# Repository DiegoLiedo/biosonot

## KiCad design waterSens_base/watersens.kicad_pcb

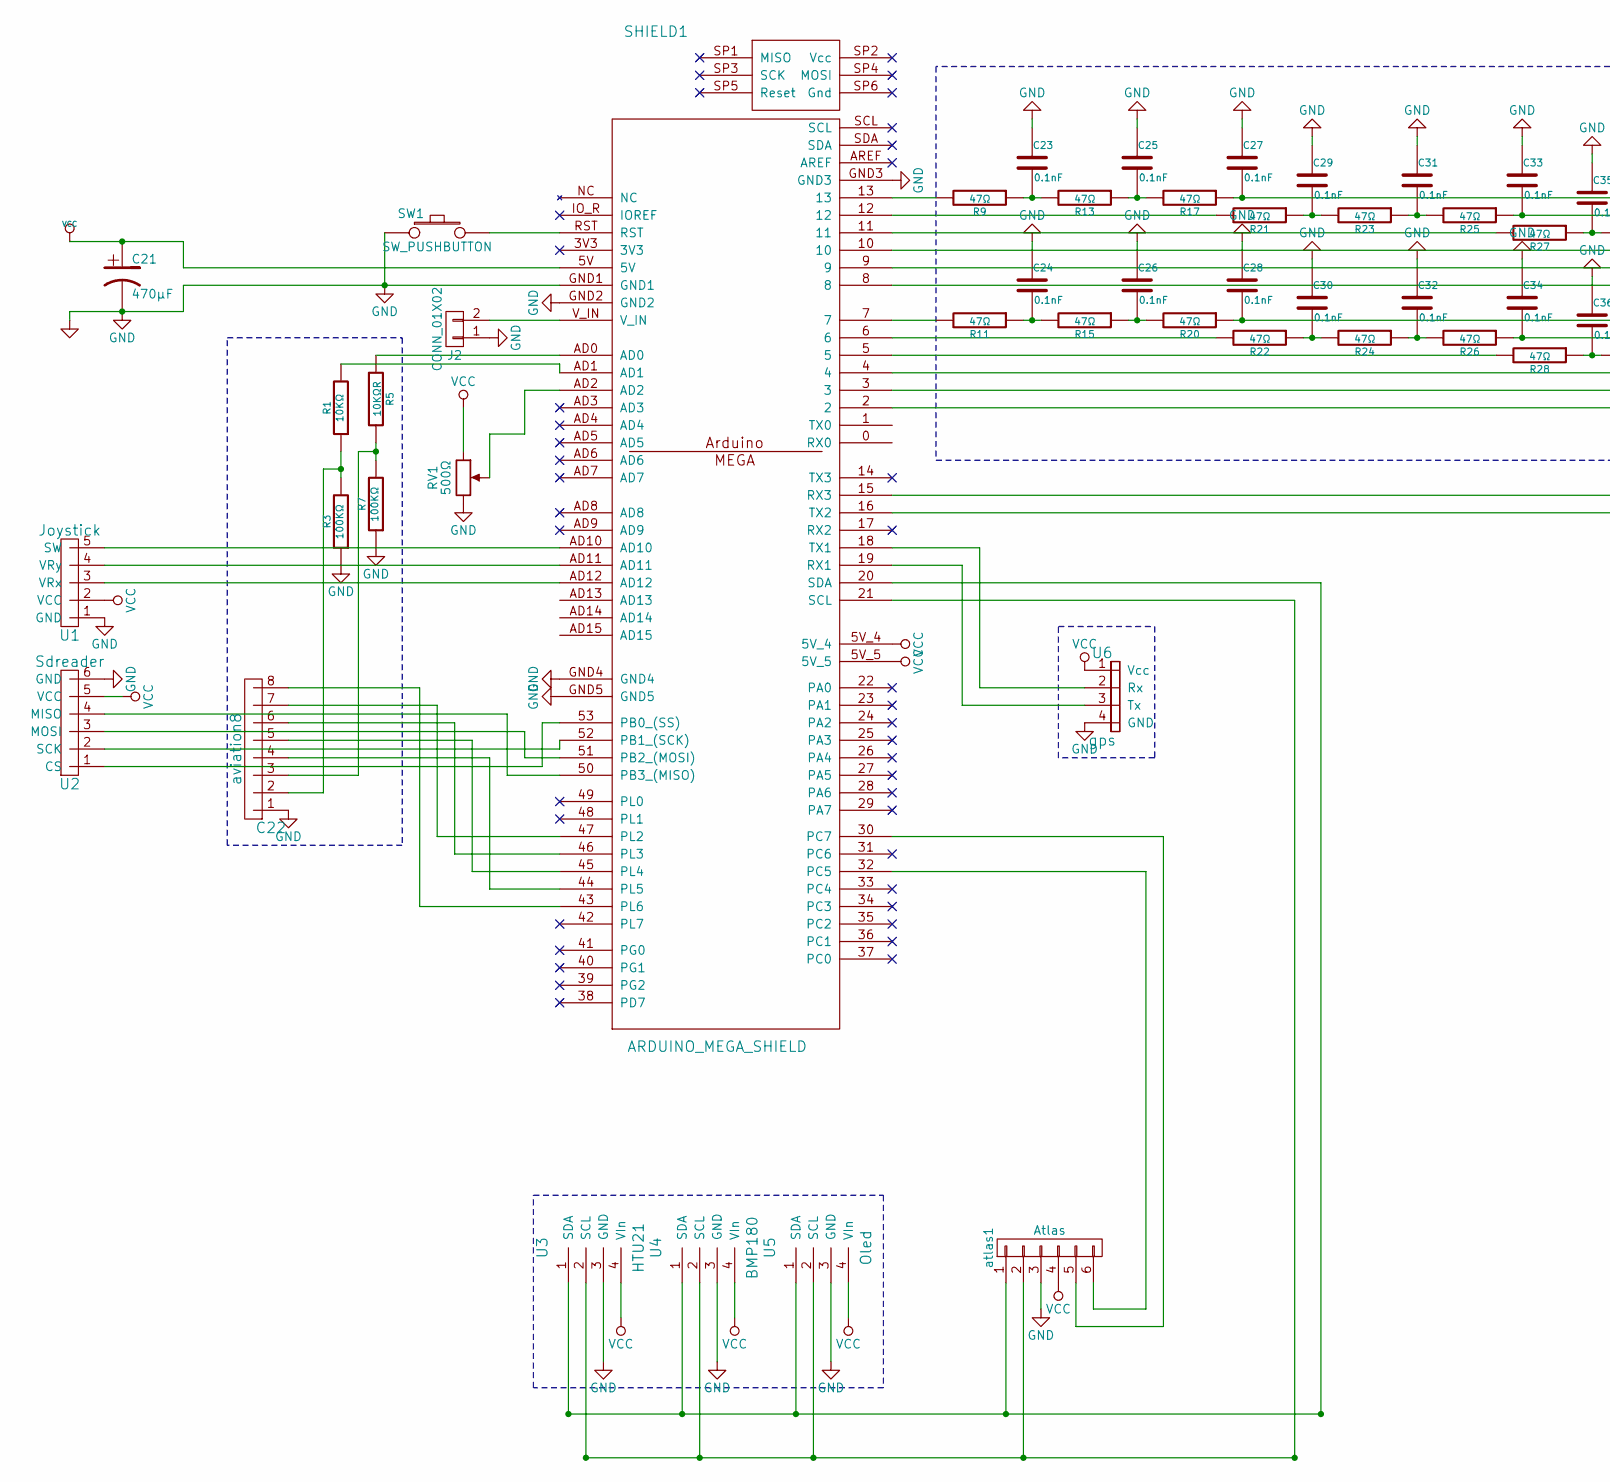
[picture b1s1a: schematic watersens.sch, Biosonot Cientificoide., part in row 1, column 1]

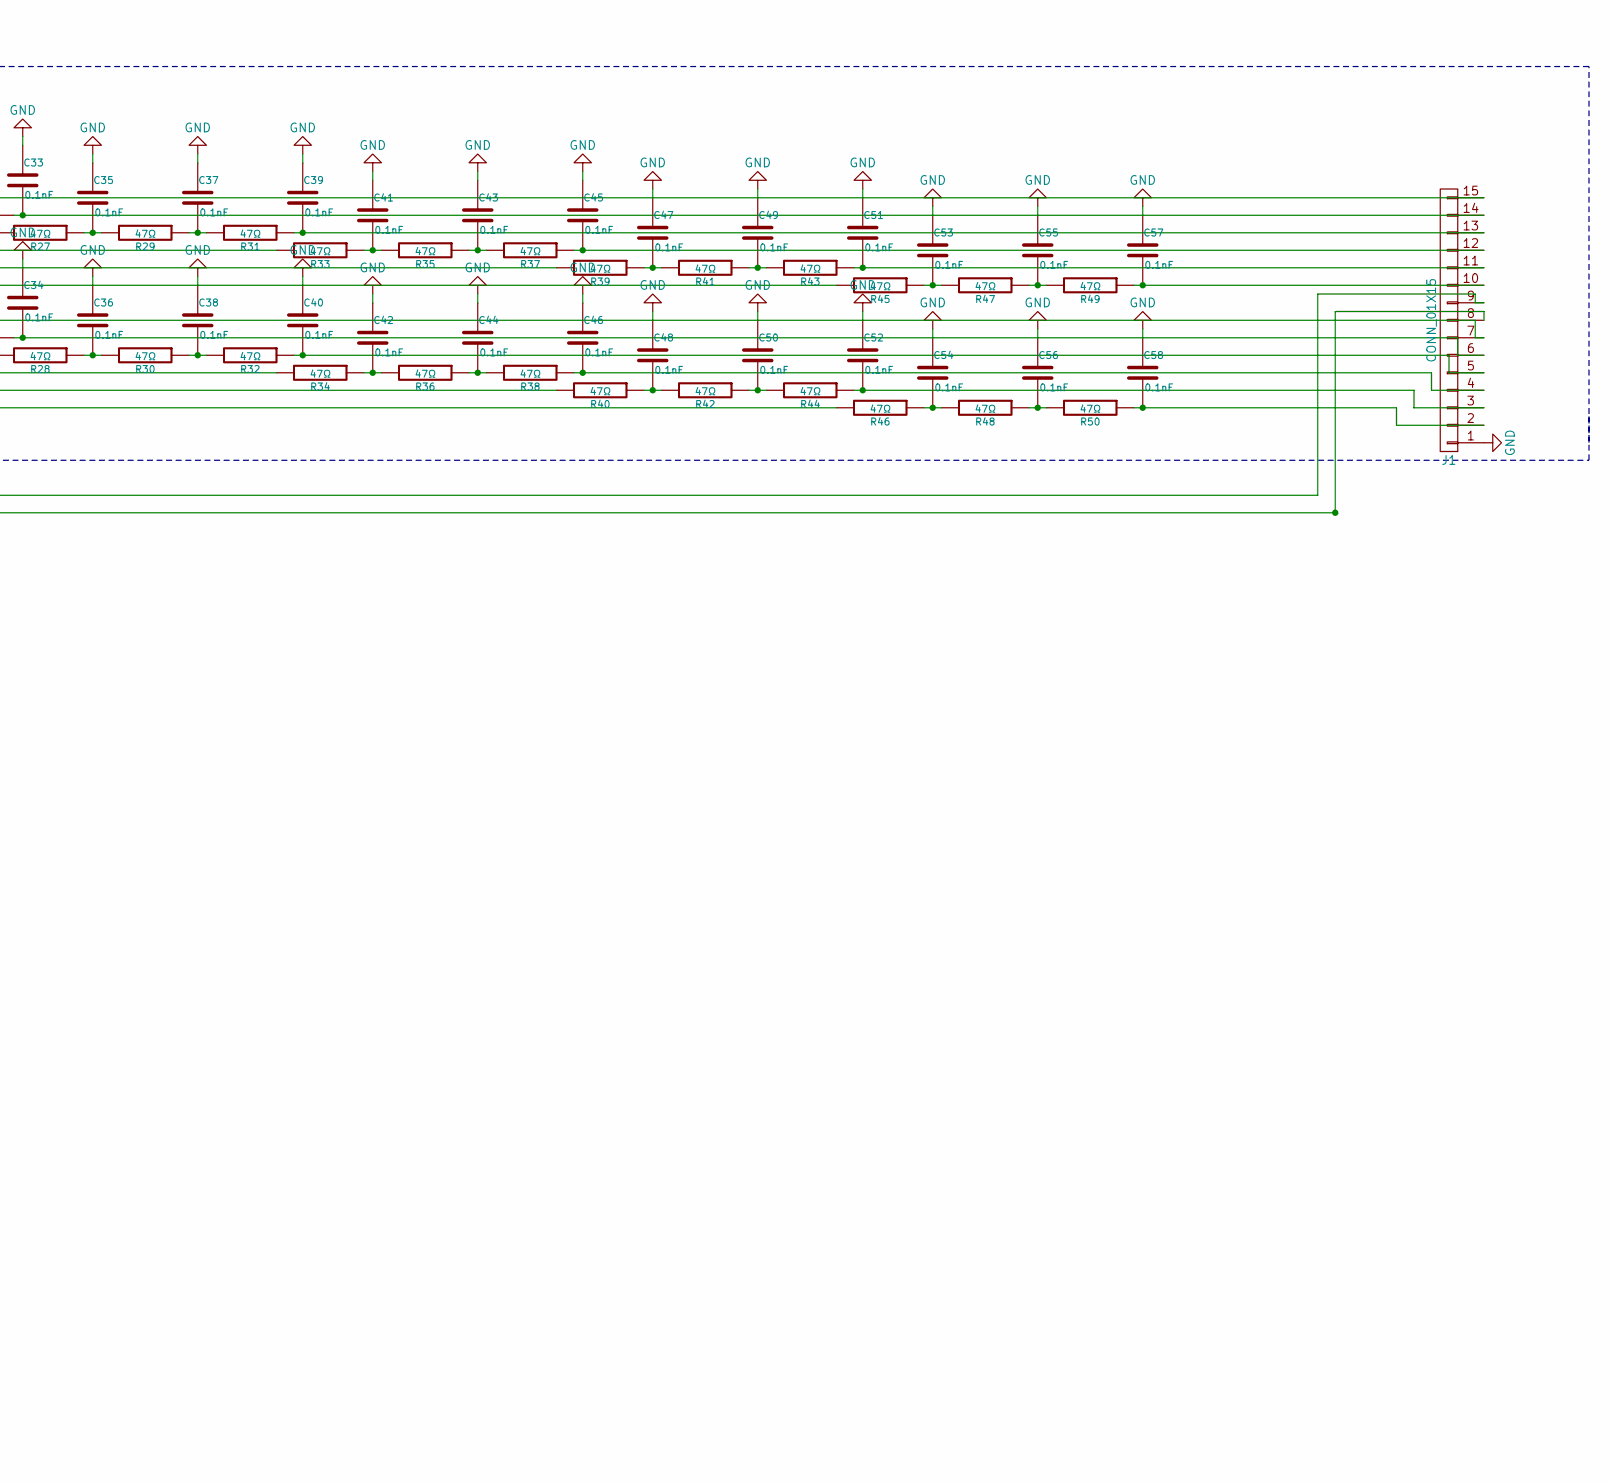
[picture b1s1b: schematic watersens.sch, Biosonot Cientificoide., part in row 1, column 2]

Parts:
C21: 470µF; c_tant_X
C22: aviation8; TerminalBlock_Pheonix_MPT-2.54mm_8pol
C23, C24, C25, C26, C27, C28, C29, C30, C31, C32, C33, C34, C35, C36, C37, C38, C39, C40, C41, C42, C43, C44, C45, C46, C47, C48, C49, C50, C51, C52, C53, C54, C55, C56, C57, C58: 0.1nF; 1206
J1: CONN_01X15; Molex_KK-6410-15_15x2.54mm_Straight
J2: CONN_01X02; TerminalBlock_Pheonix_MPT-2.54mm_2pol
R1: 10KΩ; 1206
R3, R7: 100KΩ; 1206
R5: 10KΩR; 1206
R9, R11, R13, R15, R17, R20, R21, R22, R23, R24, R25, R26, R27, R28, R29, R30, R31, R32, R33, R34, R35, R36, R37, R38, R39, R40, R41, R42, R43, R44, R45, R46, R47, R48, R49, R50: 47Ω; 1206
RV1: 500Ω; POT_RV09_VERT
SHIELD1: ARDUINO_MEGA_SHIELD
SW1: SW_PUSHBUTTON; SW_SPST_PTS645
U1: Joystick; joystick
U2: Sdreader; sdReader
U3: HTU21; I2Ca
U4: BMP180; I2Ca
U5: Oled; I2Ca
U6: gps
atlas1: Atlas; TerminalBlock_Pheonix_MPT-2.54mm_6pol

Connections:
unnamed: C22.2, R1.1, R3.2
unnamed: C22.3, R5.2, R7.2
unnamed: C22.4, SHIELD1.44 (PL5)
unnamed: C22.5, SHIELD1.45 (PL4)
unnamed: C22.6, SHIELD1.46 (PL3)
unnamed: C22.7, SHIELD1.47 (PL2)
unnamed: C22.8, SHIELD1.43 (PL6)
unnamed: C23.2, R9.1, R13.2
unnamed: C24.2, R11.1, R15.2
unnamed: C25.2, R13.1, R17.2
unnamed: C26.2, R15.1, R20.2
unnamed: C27.2, J1.15, R17.1
unnamed: C28.2, J1.7, R20.1
unnamed: C29.2, R21.1, R23.2
unnamed: C30.2, R22.1, R24.2
unnamed: C31.2, R23.1, R25.2
unnamed: C32.2, R24.1, R26.2
unnamed: C33.2, J1.14, R25.1
unnamed: C34.2, J1.6, R26.1
unnamed: C35.2, R27.1, R29.2
unnamed: C36.2, R28.1, R30.2
unnamed: C37.2, R29.1, R31.2
unnamed: C38.2, R30.1, R32.2
unnamed: C39.2, J1.13, R31.1
unnamed: C40.2, J1.5, R32.1
unnamed: C41.2, R33.1, R35.2
unnamed: C42.2, R34.1, R36.2
unnamed: C43.2, R35.1, R37.2
unnamed: C44.2, R36.1, R38.2
unnamed: C45.2, J1.12, R37.1
unnamed: C46.2, J1.4, R38.1
unnamed: C47.2, R39.1, R41.2
unnamed: C48.2, R40.1, R42.2
unnamed: C49.2, R41.1, R43.2
unnamed: C50.2, R42.1, R44.2
unnamed: C51.2, J1.11, R43.1
unnamed: C52.2, J1.3, R44.1
unnamed: C53.2, R45.1, R47.2
unnamed: C54.2, R46.1, R48.2
unnamed: C55.2, R47.1, R49.2
unnamed: C56.2, R48.1, R50.2
unnamed: C57.2, J1.10, R49.1
unnamed: C58.2, J1.2, R50.1
unnamed: J1.8, SHIELD1.16 (TX2)
unnamed: J1.9, SHIELD1.15 (RX3)
unnamed: J2.2, SHIELD1.V_IN
unnamed: R1.2, SHIELD1.AD1
unnamed: R5.1, SHIELD1.AD0
unnamed: R9.2, SHIELD1.13
unnamed: R11.2, SHIELD1.7
unnamed: R21.2, SHIELD1.12
unnamed: R22.2, SHIELD1.6
unnamed: R27.2, SHIELD1.11
unnamed: R28.2, SHIELD1.5
unnamed: R33.2, SHIELD1.10
unnamed: R34.2, SHIELD1.4
unnamed: R39.2, SHIELD1.9
unnamed: R40.2, SHIELD1.3
unnamed: R45.2, SHIELD1.8
unnamed: R46.2, SHIELD1.2
unnamed: RV1.2, SHIELD1.AD2
unnamed: SHIELD1.18 (TX1), U6.2 (Rx)
unnamed: SHIELD1.19 (RX1), U6.3 (Tx)
unnamed: SHIELD1.20 (SDA), U3.1 (SDA), U4.1 (SDA), U5.1 (SDA), atlas1.1
unnamed: SHIELD1.21 (SCL), U3.2 (SCL), U4.2 (SCL), U5.2 (SCL), atlas1.2
unnamed: SHIELD1.30 (PC7), atlas1.5
unnamed: SHIELD1.32 (PC5), atlas1.6
unnamed: SHIELD1.50 (PB3_(MISO)), U2.4 (MISO)
unnamed: SHIELD1.51 (PB2_(MOSI)), U2.3 (MOSI)
unnamed: SHIELD1.52 (PB1_(SCK)), U2.2 (SCK)
unnamed: SHIELD1.53 (PB0_(SS)), U2.1 (CS)
unnamed: SHIELD1.AD12, U1.3 (VRx)
unnamed: SHIELD1.RST, SW1.2
VCC: C21.1, RV1.1, SHIELD1.5V, SHIELD1.5V_4, SHIELD1.5V_5, U1.2 (VCC), U2.5 (VCC), U3.4 (VIn), U4.4 (VIn), U5.4 (VIn), U6.1 (Vcc), atlas1.4

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
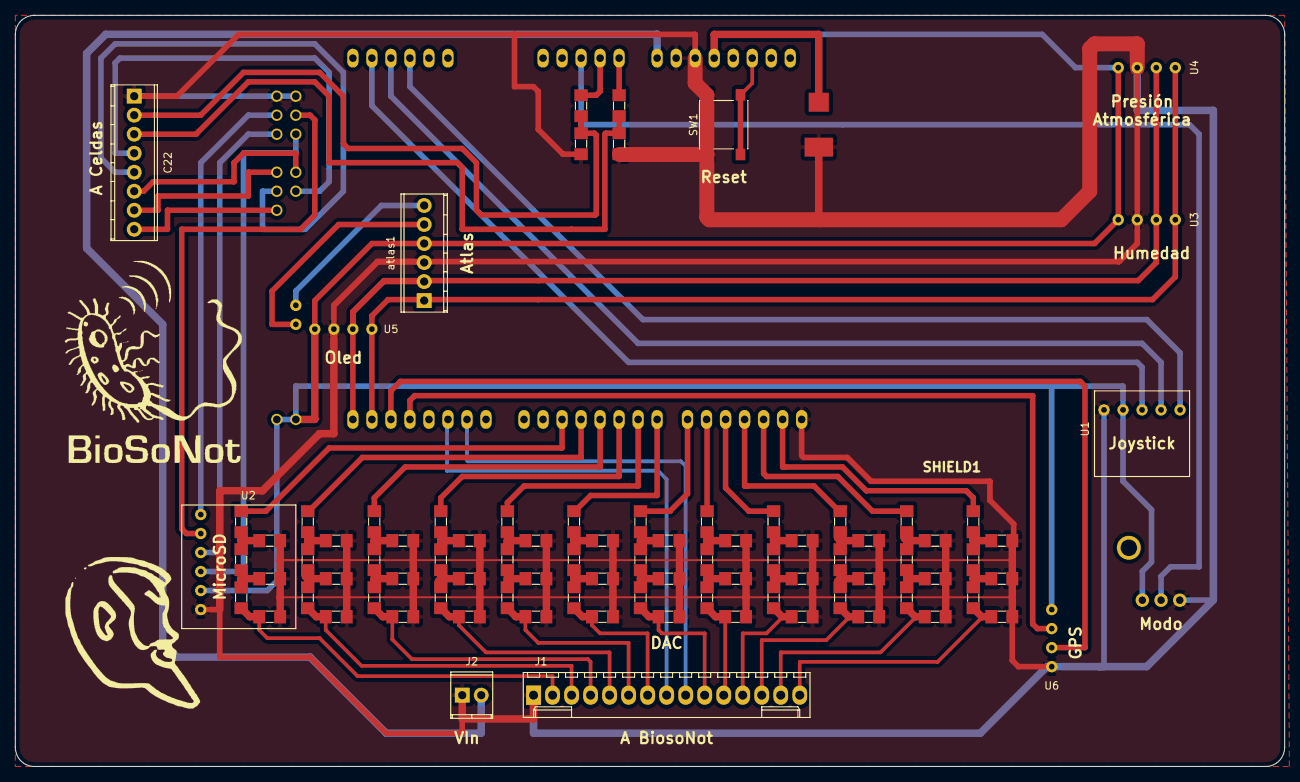
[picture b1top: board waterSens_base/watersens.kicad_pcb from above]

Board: 2 copper layers, 169.5 x 100.3 mm, 90 parts (0 on the bottom side), 77 nets.

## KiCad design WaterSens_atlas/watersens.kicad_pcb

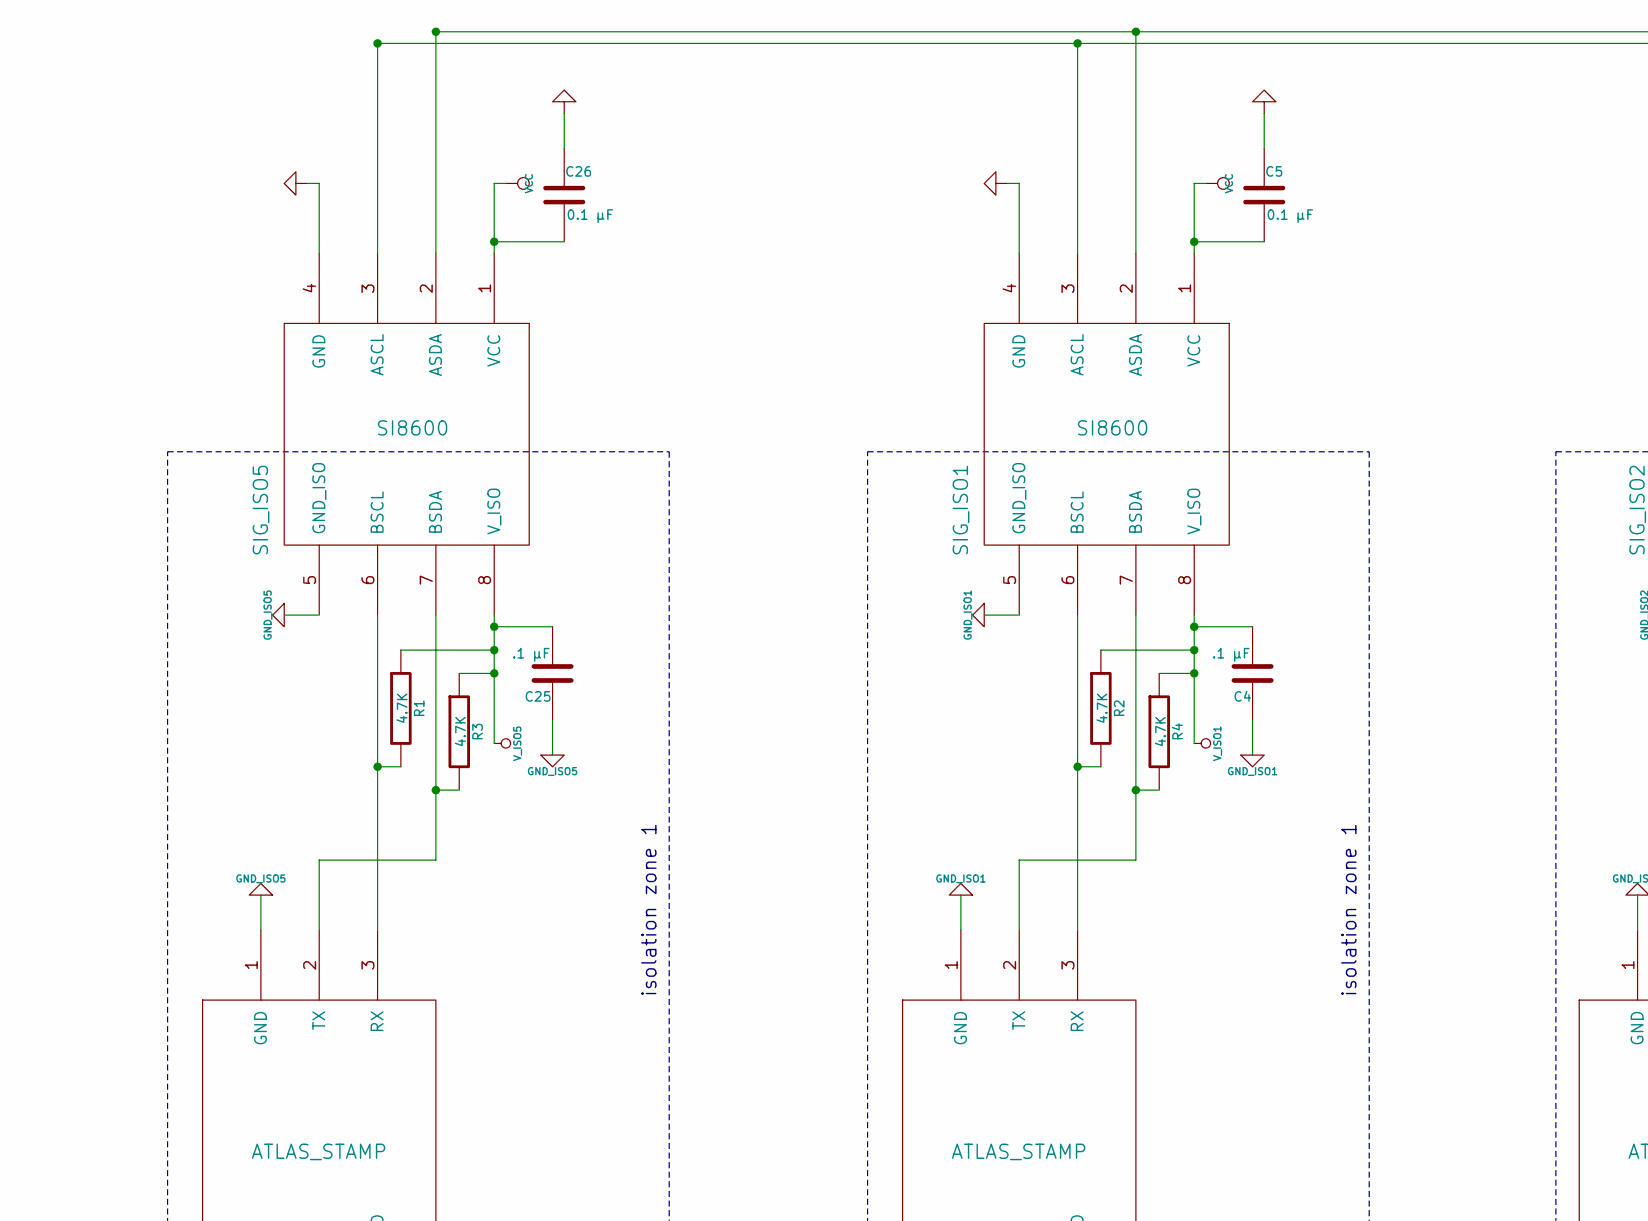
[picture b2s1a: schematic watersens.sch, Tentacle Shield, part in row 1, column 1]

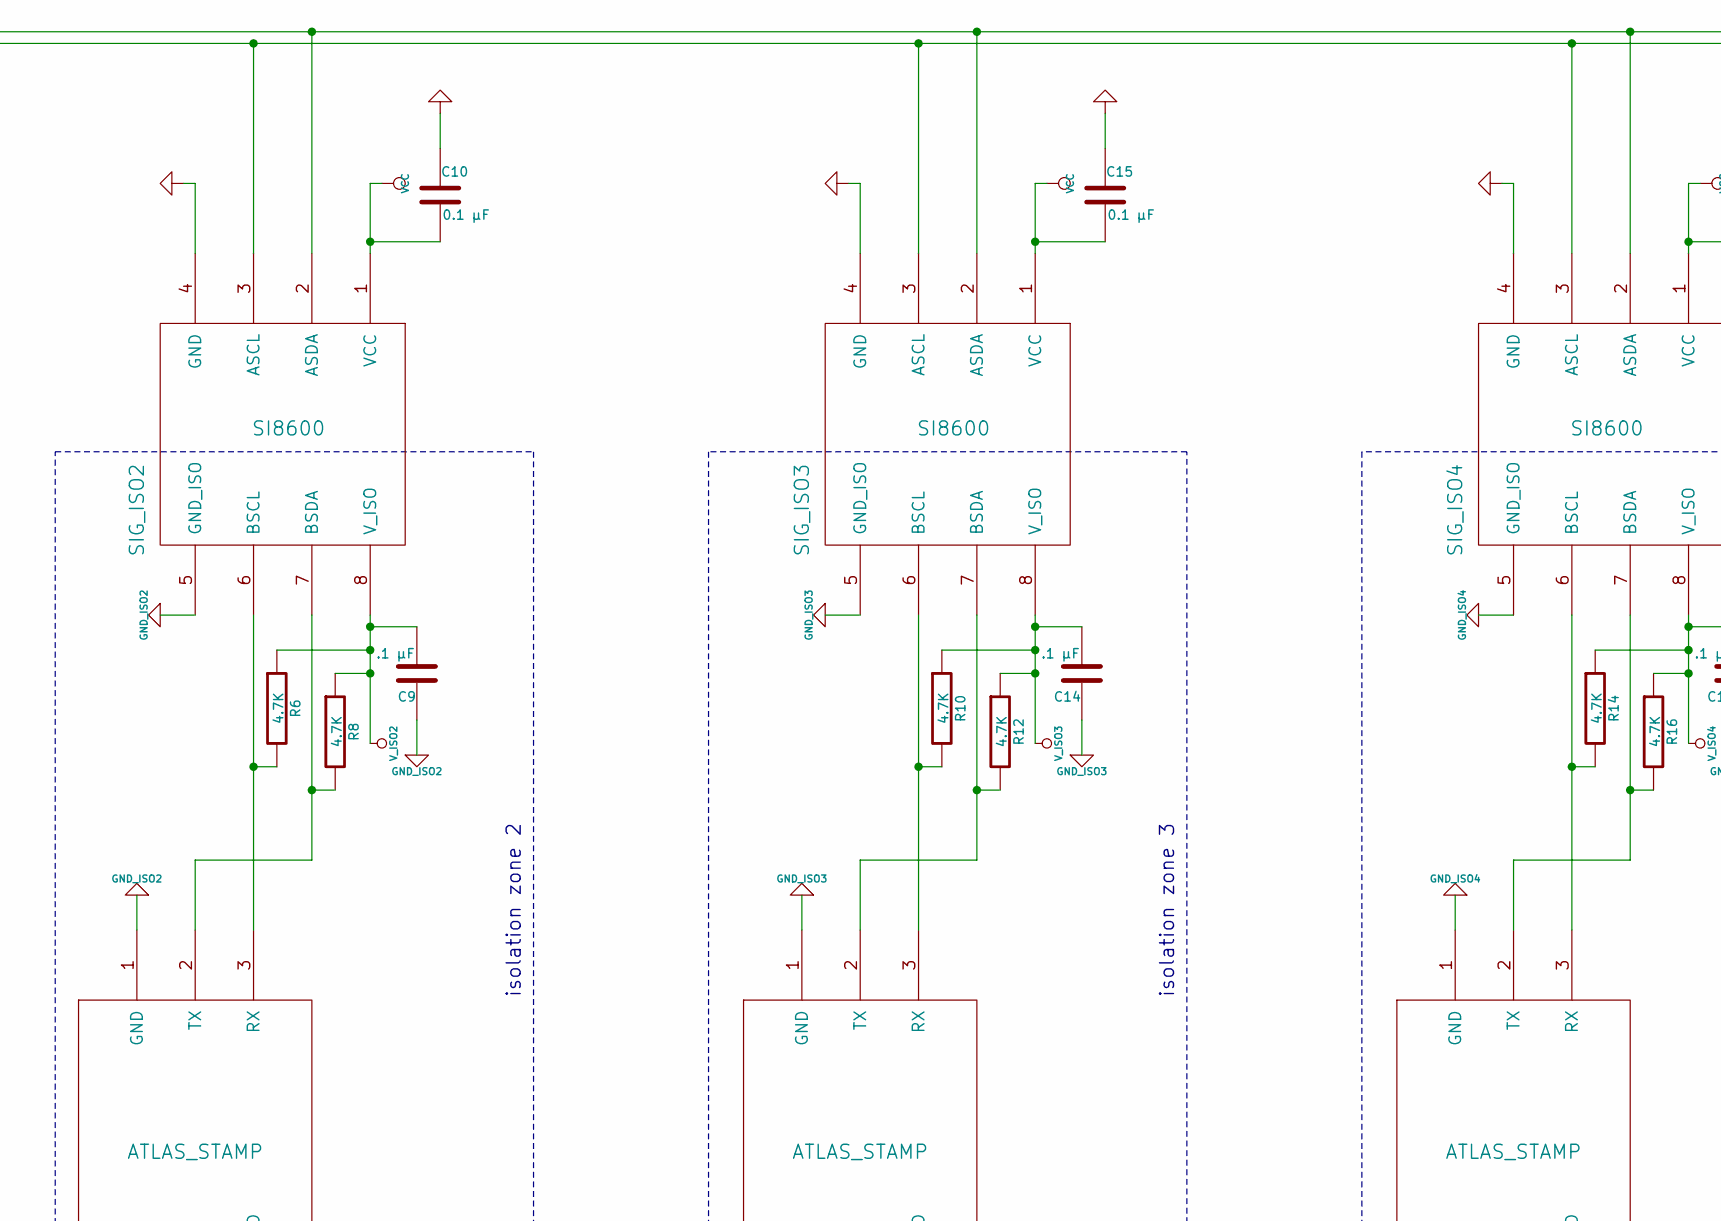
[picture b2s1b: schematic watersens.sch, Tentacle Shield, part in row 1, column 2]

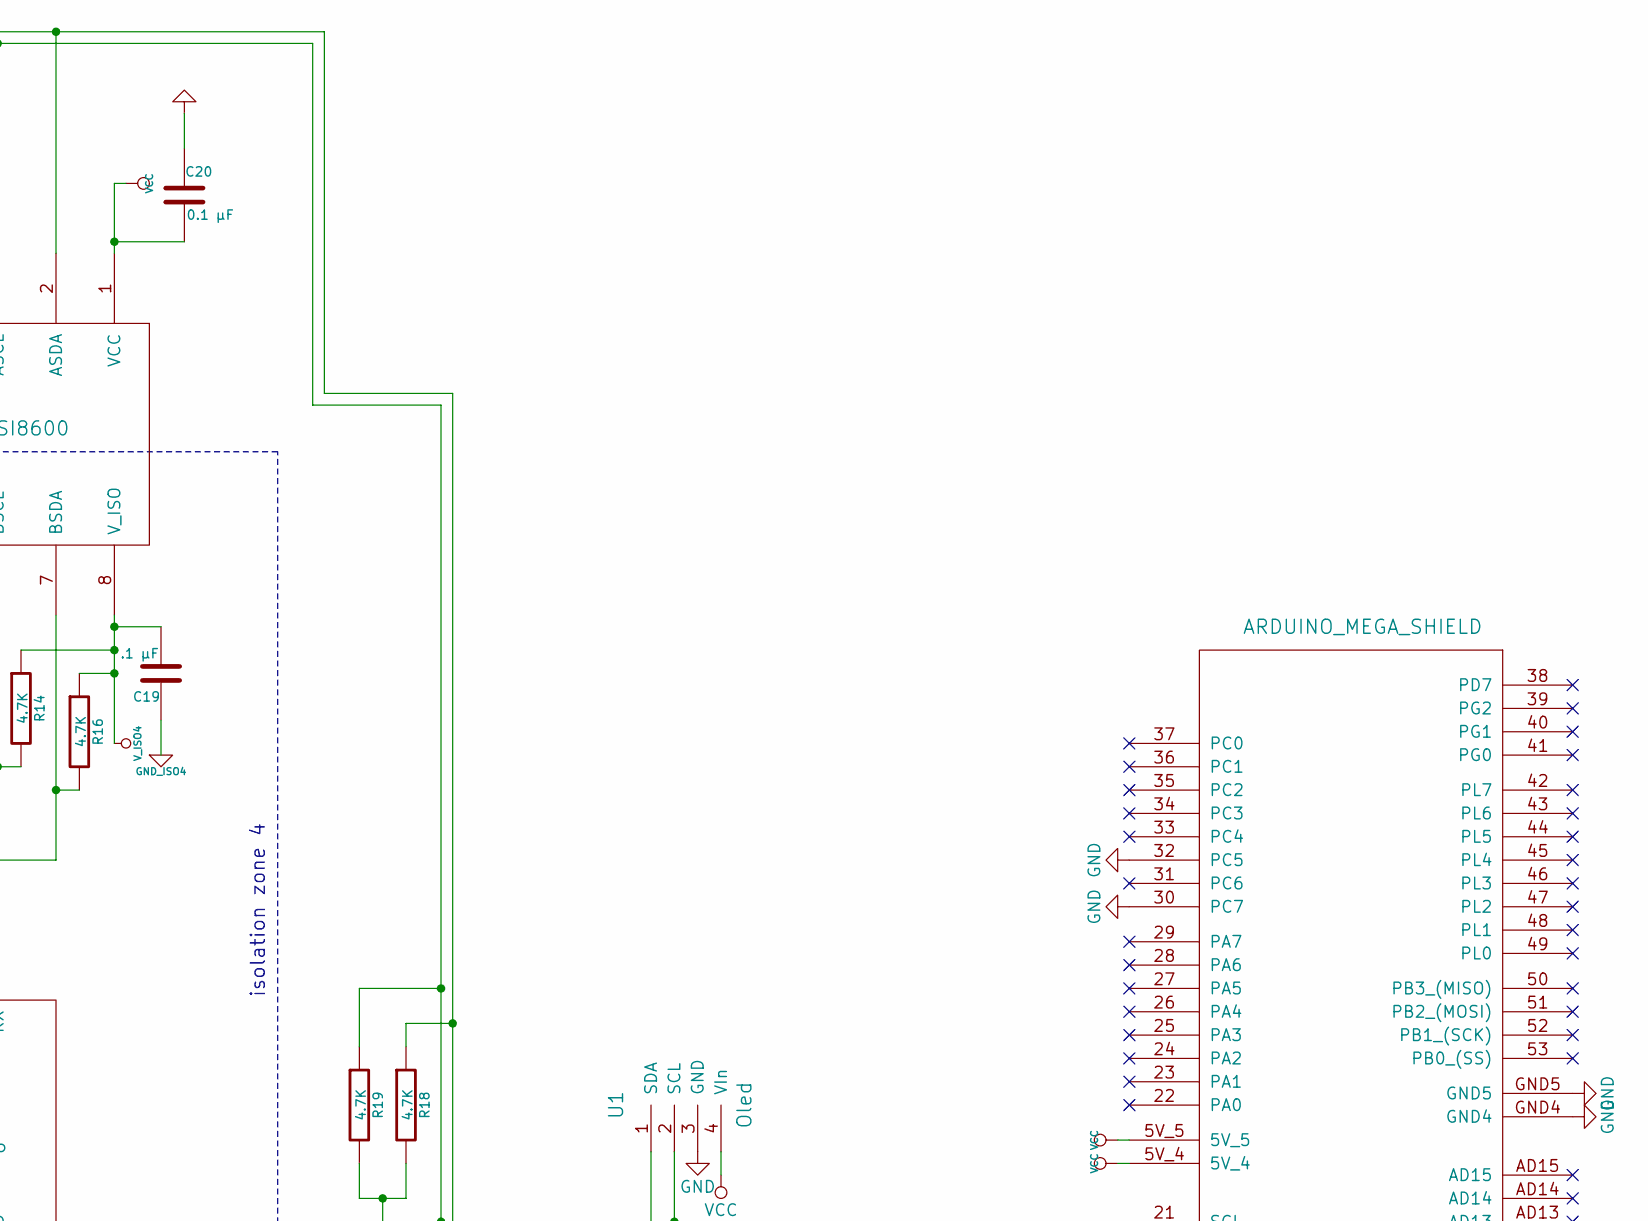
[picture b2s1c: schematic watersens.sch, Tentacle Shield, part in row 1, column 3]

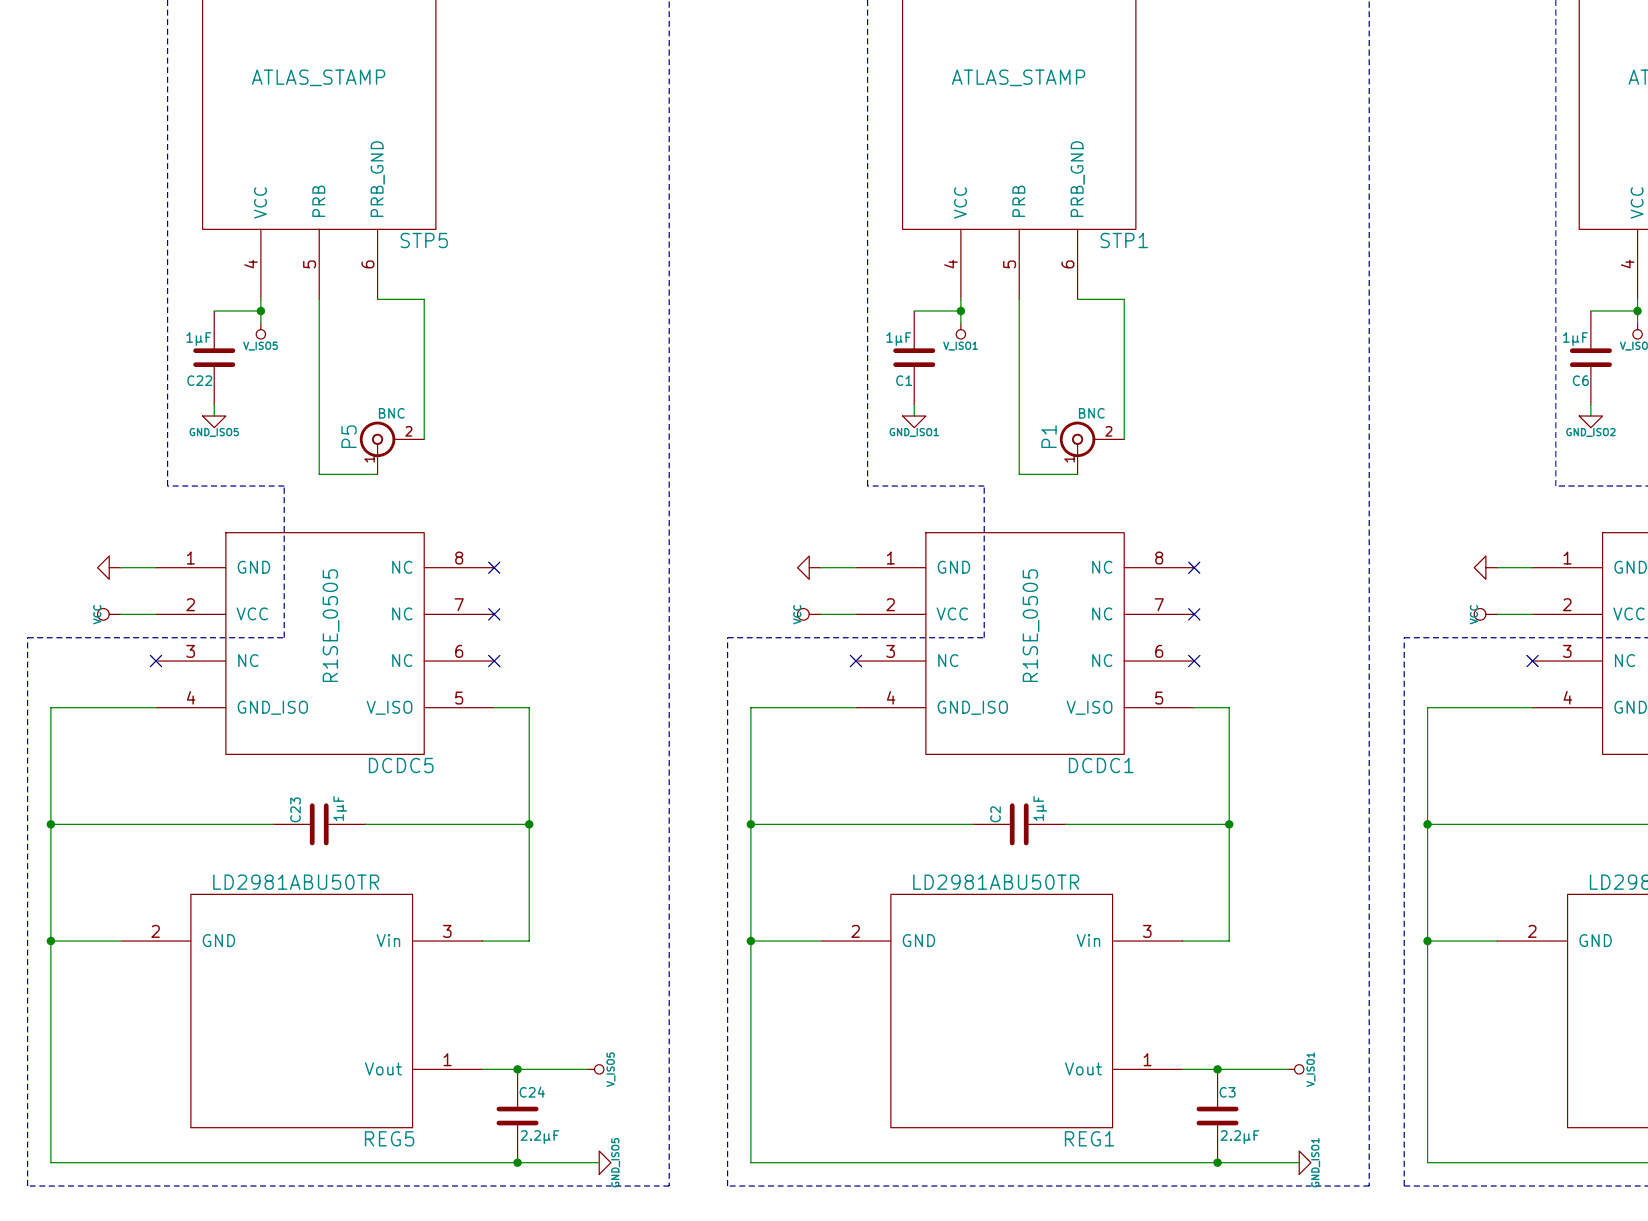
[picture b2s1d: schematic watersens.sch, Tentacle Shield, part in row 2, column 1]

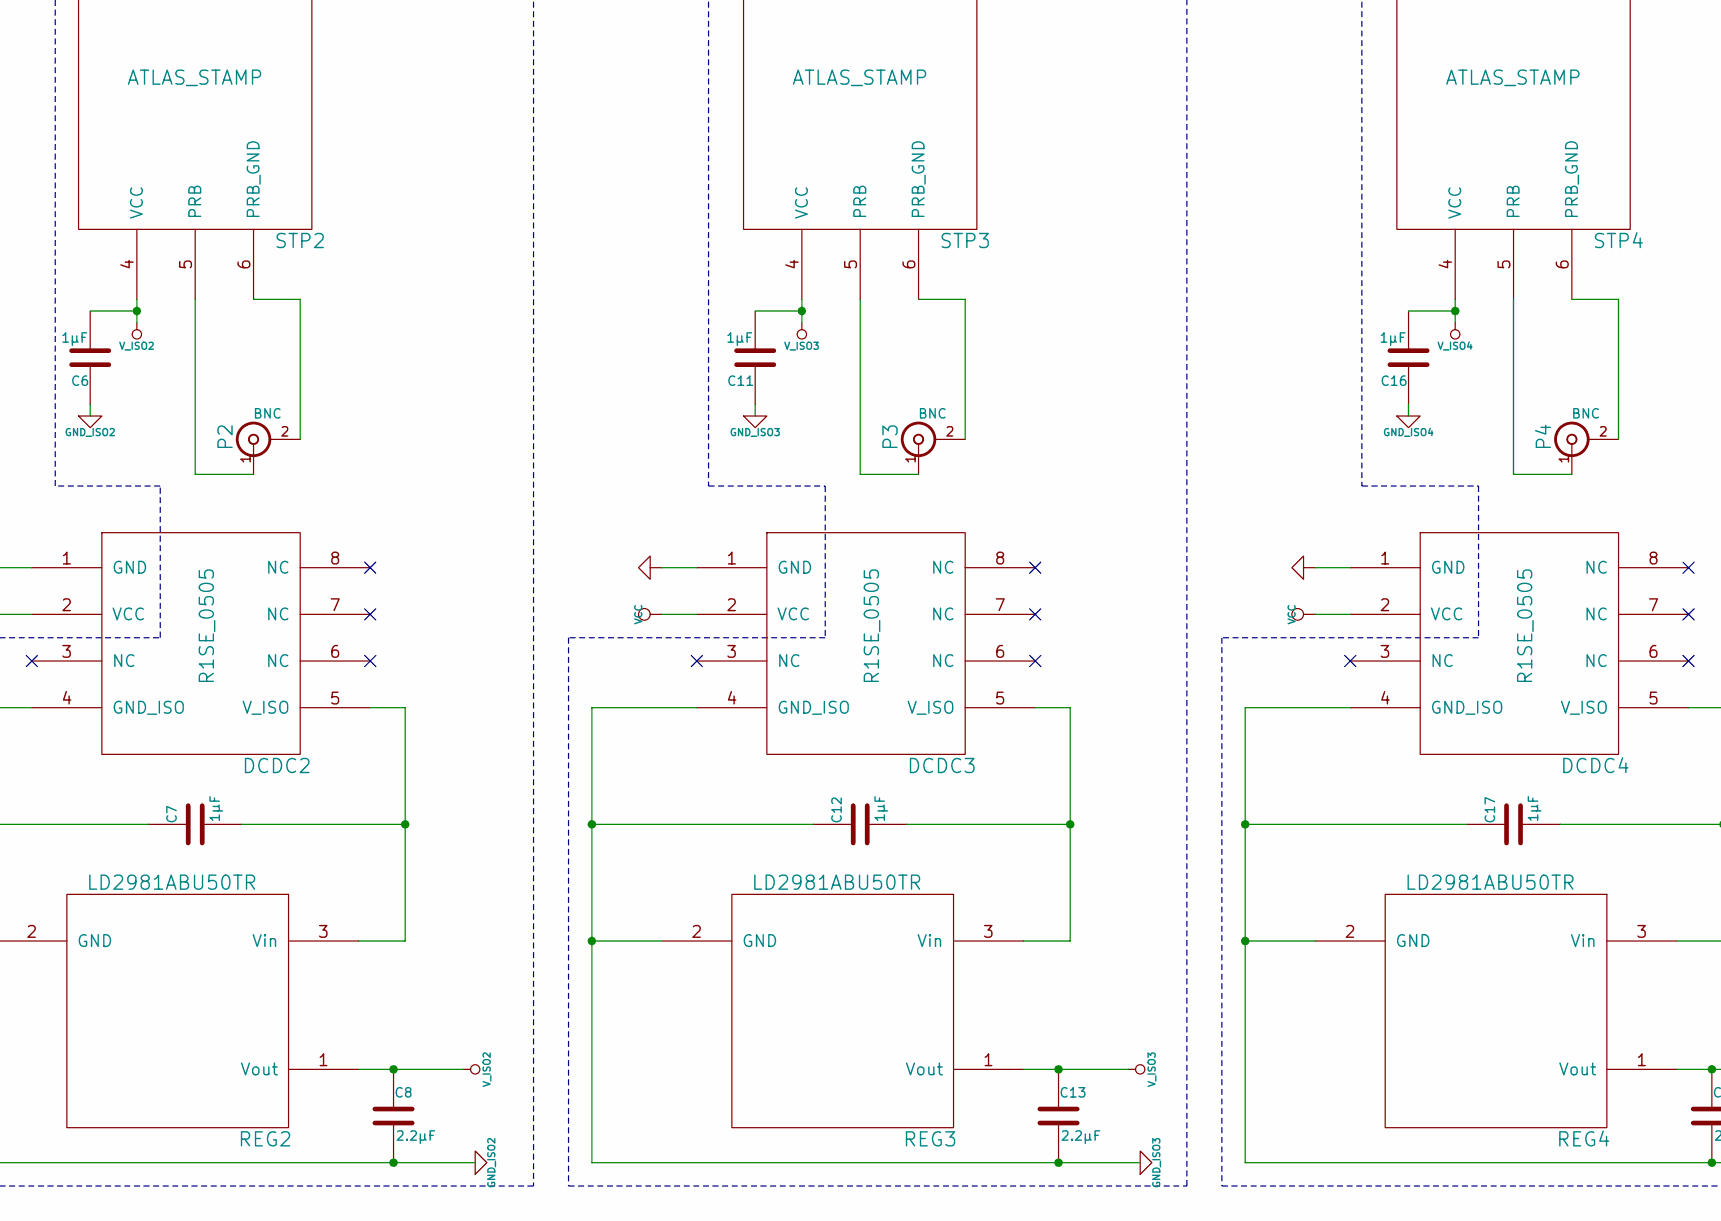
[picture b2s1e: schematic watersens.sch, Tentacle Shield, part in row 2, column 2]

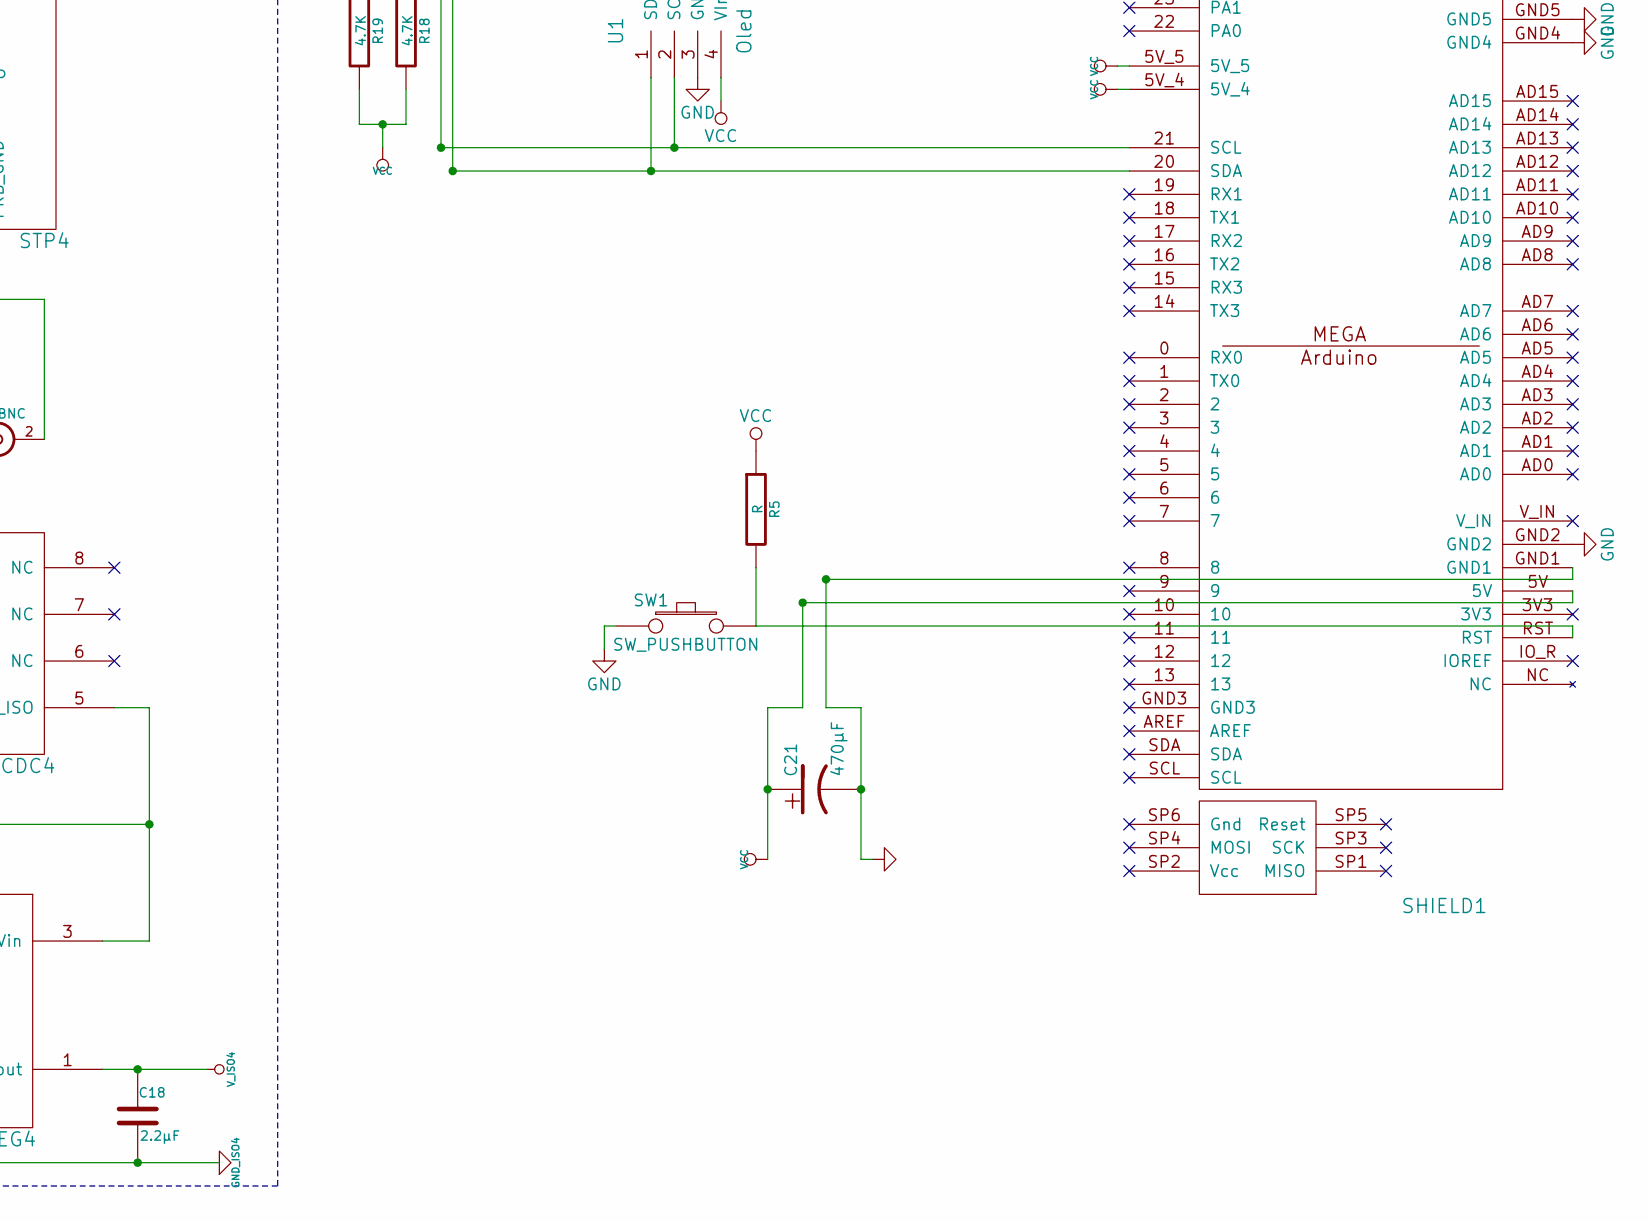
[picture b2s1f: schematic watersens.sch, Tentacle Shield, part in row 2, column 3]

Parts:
C1, C2, C6, C7, C11, C12, C16, C17, C22, C23: 1µF; C_1206_HandSoldering
C3, C8, C13, C18, C24: 2.2µF; C_1206_HandSoldering
C4, C9, C14, C19, C25: .1 µF; C_1206_HandSoldering
C5, C10, C15, C20, C26: 0.1 µF; C_1206_HandSoldering
C21: 470µF; c_tant_X
DCDC1, DCDC2, DCDC3, DCDC4, DCDC5: R1SE_0505
P1, P2, P3, P4, P5: BNC; BNC-1337543a
R1, R2, R3, R4, R6, R8, R10, R12, R14, R16, R18, R19: 4.7K; R_1206_HandSoldering
R5: R; R_1206_HandSoldering
REG1, REG2, REG3, REG4, REG5: LD2981ABU50TR; sot89
SHIELD1: ARDUINO_MEGA_SHIELD; MEGA_SHIELD2
SIG_ISO1, SIG_ISO2, SIG_ISO3, SIG_ISO4, SIG_ISO5: SI8600; so-8a
STP1, STP2, STP3, STP4, STP5: ATLAS_STAMP; Atlas_Stamp
SW1: SW_PUSHBUTTON; SW_PUSH_6mm
U1: Oled; I2Ca

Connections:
GND: C5.1, C10.1, C15.1, C20.1, C21.2, C26.1, DCDC1.1 (GND), DCDC2.1 (GND), DCDC3.1 (GND), DCDC4.1 (GND), DCDC5.1 (GND), SHIELD1.30 (PC7), SHIELD1.32 (PC5), SHIELD1.GND1, SHIELD1.GND2, SHIELD1.GND4, SHIELD1.GND5, SIG_ISO1.4 (GND), SIG_ISO2.4 (GND), SIG_ISO3.4 (GND), SIG_ISO4.4 (GND), SIG_ISO5.4 (GND), SW1.1, U1.3 (GND)
GND_ISO1: C1.1, C2.1, C3.2, C4.1, DCDC1.4 (GND_ISO), REG1.2 (GND), SIG_ISO1.5 (GND_ISO), STP1.1 (GND)
GND_ISO2: C6.1, C7.1, C8.2, C9.1, DCDC2.4 (GND_ISO), REG2.2 (GND), SIG_ISO2.5 (GND_ISO), STP2.1 (GND)
GND_ISO3: C11.1, C12.1, C13.2, C14.1, DCDC3.4 (GND_ISO), REG3.2 (GND), SIG_ISO3.5 (GND_ISO), STP3.1 (GND)
GND_ISO4: C16.1, C17.1, C18.2, C19.1, DCDC4.4 (GND_ISO), REG4.2 (GND), SIG_ISO4.5 (GND_ISO), STP4.1 (GND)
GND_ISO5: C22.1, C23.1, C24.2, C25.1, DCDC5.4 (GND_ISO), REG5.2 (GND), SIG_ISO5.5 (GND_ISO), STP5.1 (GND)
unnamed: C2.2, DCDC1.5 (V_ISO), REG1.3 (Vin)
unnamed: C7.2, DCDC2.5 (V_ISO), REG2.3 (Vin)
unnamed: C12.2, DCDC3.5 (V_ISO), REG3.3 (Vin)
unnamed: C17.2, DCDC4.5 (V_ISO), REG4.3 (Vin)
unnamed: C23.2, DCDC5.5 (V_ISO), REG5.3 (Vin)
unnamed: P1.1 (In), STP1.5 (PRB)
unnamed: P1.2 (Ext), STP1.6 (PRB_GND)
unnamed: P2.1 (In), STP2.5 (PRB)
unnamed: P2.2 (Ext), STP2.6 (PRB_GND)
unnamed: P3.1 (In), STP3.5 (PRB)
unnamed: P3.2 (Ext), STP3.6 (PRB_GND)
unnamed: P4.1 (In), STP4.5 (PRB)
unnamed: P4.2 (Ext), STP4.6 (PRB_GND)
unnamed: P5.1 (In), STP5.5 (PRB)
unnamed: P5.2 (Ext), STP5.6 (PRB_GND)
unnamed: R1.2, SIG_ISO5.6 (BSCL), STP5.3 (RX)
unnamed: R2.2, SIG_ISO1.6 (BSCL), STP1.3 (RX)
unnamed: R3.2, SIG_ISO5.7 (BSDA), STP5.2 (TX)
unnamed: R4.2, SIG_ISO1.7 (BSDA), STP1.2 (TX)
unnamed: R5.2, SHIELD1.RST, SW1.2
unnamed: R6.2, SIG_ISO2.6 (BSCL), STP2.3 (RX)
unnamed: R8.2, SIG_ISO2.7 (BSDA), STP2.2 (TX)
unnamed: R10.2, SIG_ISO3.6 (BSCL), STP3.3 (RX)
unnamed: R12.2, SIG_ISO3.7 (BSDA), STP3.2 (TX)
unnamed: R14.2, SIG_ISO4.6 (BSCL), STP4.3 (RX)
unnamed: R16.2, SIG_ISO4.7 (BSDA), STP4.2 (TX)
unnamed: R18.1, SHIELD1.20 (SDA), SIG_ISO1.2 (ASDA), SIG_ISO2.2 (ASDA), SIG_ISO3.2 (ASDA), SIG_ISO4.2 (ASDA), SIG_ISO5.2 (ASDA), U1.1 (SDA)
unnamed: R19.1, SHIELD1.21 (SCL), SIG_ISO1.3 (ASCL), SIG_ISO2.3 (ASCL), SIG_ISO3.3 (ASCL), SIG_ISO4.3 (ASCL), SIG_ISO5.3 (ASCL), U1.2 (SCL)
VCC: C5.2, C10.2, C15.2, C20.2, C21.1, C26.2, DCDC1.2 (VCC), DCDC2.2 (VCC), DCDC3.2 (VCC), DCDC4.2 (VCC), DCDC5.2 (VCC), R5.1, R18.2, R19.2, SHIELD1.5V, SHIELD1.5V_4, SHIELD1.5V_5, SIG_ISO1.1 (VCC), SIG_ISO2.1 (VCC), SIG_ISO3.1 (VCC), SIG_ISO4.1 (VCC), SIG_ISO5.1 (VCC), U1.4 (VIn)
V_ISO1: C1.2, C3.1, C4.2, R2.1, R4.1, REG1.1 (Vout), SIG_ISO1.8 (V_ISO), STP1.4 (VCC)
V_ISO2: C6.2, C8.1, C9.2, R6.1, R8.1, REG2.1 (Vout), SIG_ISO2.8 (V_ISO), STP2.4 (VCC)
V_ISO3: C11.2, C13.1, C14.2, R10.1, R12.1, REG3.1 (Vout), SIG_ISO3.8 (V_ISO), STP3.4 (VCC)
V_ISO4: C16.2, C18.1, C19.2, R14.1, R16.1, REG4.1 (Vout), SIG_ISO4.8 (V_ISO), STP4.4 (VCC)
V_ISO5: C22.2, C24.1, C25.2, R1.1, R3.1, REG5.1 (Vout), SIG_ISO5.8 (V_ISO), STP5.4 (VCC)

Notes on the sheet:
isolation zone 1
isolation zone 2
isolation zone 3
isolation zone 4
